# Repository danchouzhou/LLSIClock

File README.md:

# Nuvoton Visual Studio Code Template
## Usage
### To clone this project
This project work with submodule from Nuvoton corporation. You need to initialize submodules by passing ``--recurse-submodules`` to the ``git clone`` command.
```
git clone https://github.com/danchouzhou/Nuvoton-VScode-template.git --recurse-submodules
```

### Build tools
#### Windows users
Since we use VScode ``setting.json`` provide the build environment, only the execution binary need to be download (without installing). Download the following files, extract to the path ``C:\Users\"Your user name"\BuildTools\Windows`` which specific in ``.vscode/setting.json``.
- [gcc-arm-none-eabi-10.3-2021.07-win32.zip](https://developer.arm.com/downloads/-/gnu-rm)
- [xpack-windows-build-tools-4.3.0-1-win32-x64.zip
](https://github.com/xpack-dev-tools/windows-build-tools-xpack/releases/tag/v4.3.0-1)
- [OpenOCD-Nuvoton](https://github.com/OpenNuvoton/OpenOCD-Nuvoton/releases)
#### Linux users
- [gcc-arm-none-eabi-10.3-2021.07-x86_64-linux.tar.bz2](https://developer.arm.com/downloads/-/gnu-rm)
- [OpenOCD-Nuvoton](https://github.com/OpenNuvoton/OpenOCD-Nuvoton/releases)
```
mkdir -p ~/BuildTools/Linux/
tar jxvf gcc-arm-none-eabi-10.3-2021.07-x86_64-linux.tar.bz2 -C ~/BuildTools/Linux/
unzip OpenOCD_Linux.zip -d ~/BuildTools/Linux/
chmod +x ~/BuildTools/Linux/OpenOCD/bin/openocd
```
- GNU Make should be installed.
```
sudo apt install make
```
### Build the template
If you want to build the target for Nuvoton M480 series for example. Open a terminal inside the VScode.
```
cd firmware/LLSI_RGBW
```
Simply ``make``. ``LLSI_RGBW.bin`` should be inside the ``Objects`` folder.
```
make
```
### Flash the firmware
```
make flash
```
For Linux users, probably need to add the access permission for usb device.
```
sudo chmod -R 777 /dev/bus/usb/
```
### Rebuild
```
make clean
make
```

### Create your own project from this template
1. Add BSP submodule from [OpenNuvoton](https://github.com/OpenNuvoton). For example:
```
git submodule add https://github.com/OpenNuvoton/M480BSP.git NuMicro-M4/M480BSP
```
2. Edit ``CORTEX_M``, ``BASE``, ``DEVICE`` in the ``makefile.conf``.

## Reference
- [A Simple Makefile Tutorial](https://www.cs.colby.edu/maxwell/courses/tutorials/maketutor/)
- [Makefile Tutorial By Example](https://makefiletutorial.com/)
- [Git - Submodules](https://git-scm.com/book/en/v2/Git-Tools-Submodules)
- [Set global $PATH environment variable in VS Code - Stack Overflow](https://stackoverflow.com/questions/43983718/set-global-path-environment-variable-in-vs-code)
- [Flashing firmware with OpenOCD without using telnet](https://acassis.wordpress.com/2016/08/22/flashing-firmware-with-openocd-without-using-telnet/)

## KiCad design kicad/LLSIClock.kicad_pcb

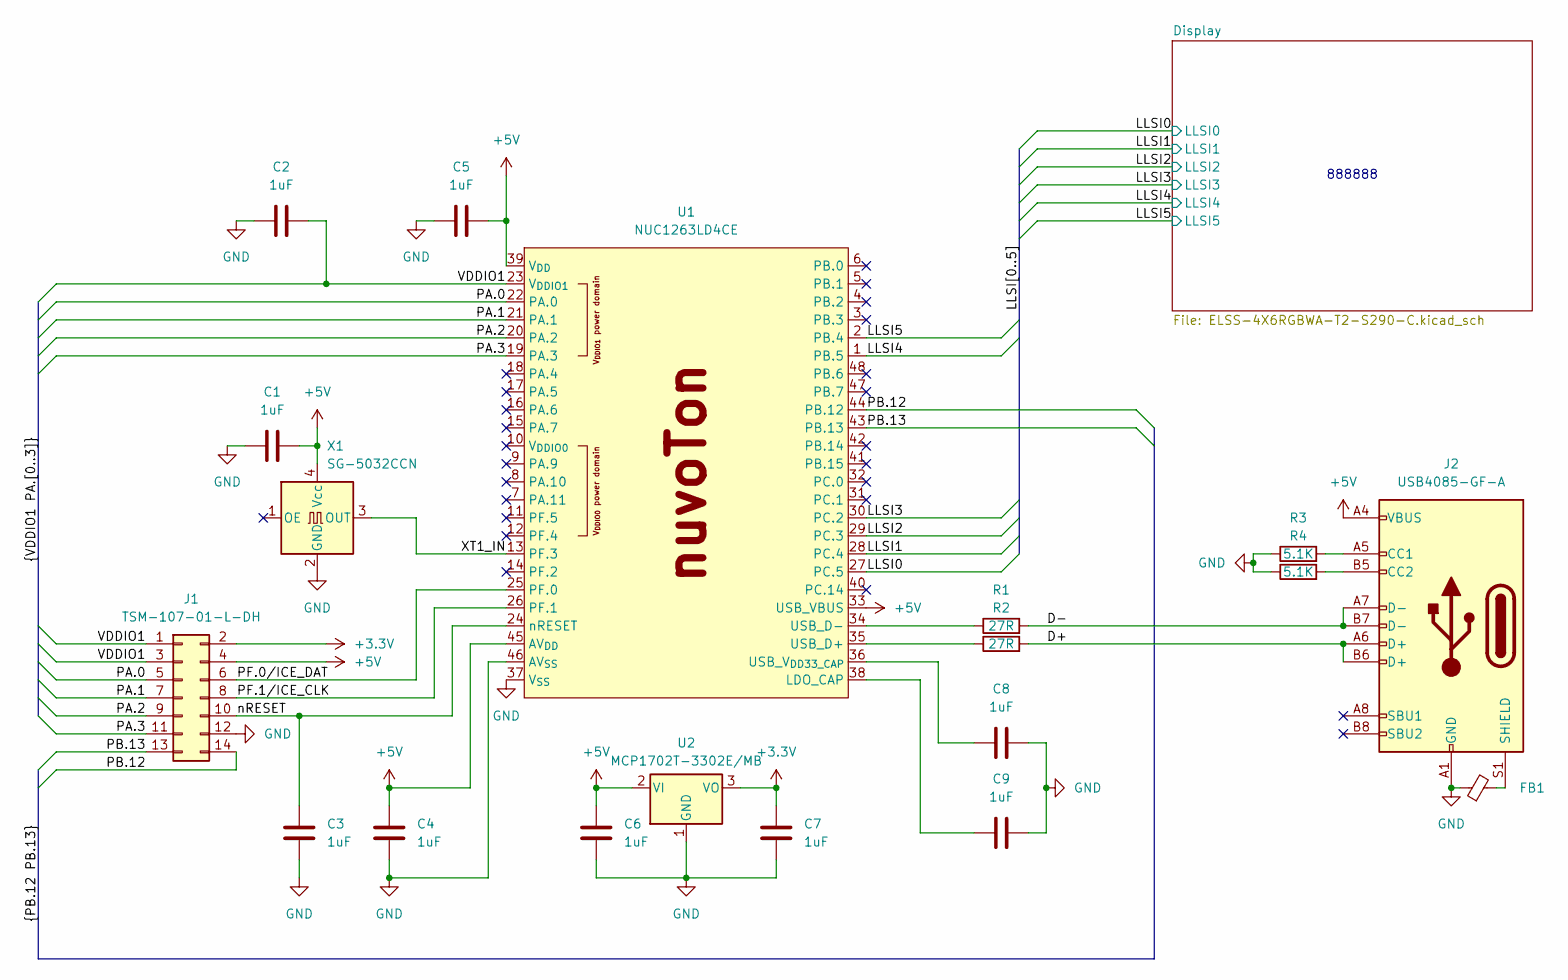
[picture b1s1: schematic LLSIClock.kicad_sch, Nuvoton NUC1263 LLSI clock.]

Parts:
C1, C2, C3, C4, C5, C6, C7, C8, C9: 1uF; C_0805_2012Metric
FB1: FerriteBead_Small; L_0805_2012Metric
J1: TSM-107-01-L-DH
J2: USB4085-GF-A; 2137160001_USB4085
R1, R2: 27R; R_0805_2012Metric
R3, R4: 5.1K; R_0805_2012Metric
U1: NUC1263LD4CE; LQFP-48_7x7mm_P0.5mm
U2: MCP1702T-3302E/MB; SOT-89-3
X1: SG-5032CCN; Oscillator_SMD_SeikoEpson_SG8002LB-4Pin_5.0x3.2mm

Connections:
+3.3V: C7.1, J1.2, U2.3 (VO)
+5V: C1.2, C4.1, C5.2, C6.1, J1.4, J2.A4 (VBUS), J2.A9 (VBUS), J2.B4 (VBUS), J2.B9 (VBUS), U1.33 (USB_VBUS), U1.39 (V_{DD}), U1.45 (AV_{DD}), U2.2 (VI), X1.4 (Vcc); also elsewhere on the board
/D+: J2.A6 (D+), J2.B6 (D+), R2.2
/D-: J2.A7 (D-), J2.B7 (D-), R1.2
/LLSI0: U1.27 (PC.5); also elsewhere on the board
/LLSI1: U1.28 (PC.4); also elsewhere on the board
/LLSI2: U1.29 (PC.3); also elsewhere on the board
/LLSI3: U1.30 (PC.2); also elsewhere on the board
/LLSI4: U1.1 (PB.5); also elsewhere on the board
/LLSI5: U1.2 (PB.4); also elsewhere on the board
/PA.0: J1.5, U1.22 (PA.0)
/PA.1: J1.7, U1.21 (PA.1)
/PA.2: J1.9, U1.20 (PA.2)
/PA.3: J1.11, U1.19 (PA.3)
/PB.12: J1.14, U1.44 (PB.12)
/PB.13: J1.13, U1.43 (PB.13)
/PF.0/ICE_DAT: J1.6, U1.25 (PF.0)
/PF.1/ICE_CLK: J1.8, U1.26 (PF.1)
/VDDIO1: C2.2, J1.1, J1.3, U1.23 (V_{DDIO1})
/XT1_IN: U1.13 (PF.3), X1.3 (OUT)
/nRESET: C3.1, J1.10, U1.24 (nRESET)
GND: C1.1, C2.1, C3.2, C4.2, C5.1, C6.2, C7.2, C8.2, C9.2, FB1.1, J1.12, J2.A1 (GND), J2.A12 (GND), J2.B1 (GND), J2.B12 (GND), R3.1, R4.1, U1.37 (V_{SS}), U1.46 (AV_{SS}), U2.1 (GND), X1.2 (GND); also elsewhere on the board
unnamed: J2.A5 (CC1), R3.2
unnamed: J2.B5 (CC2), R4.2
unnamed: FB1.2, J2.S1 (SHIELD)
unnamed: C9.1, U1.38 (LDO_CAP)
unnamed: R2.1, U1.35 (USB_D+)
unnamed: R1.1, U1.34 (USB_D-)
unnamed: C8.1, U1.36 (USB_V_{DD33_CAP})

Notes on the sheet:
888888

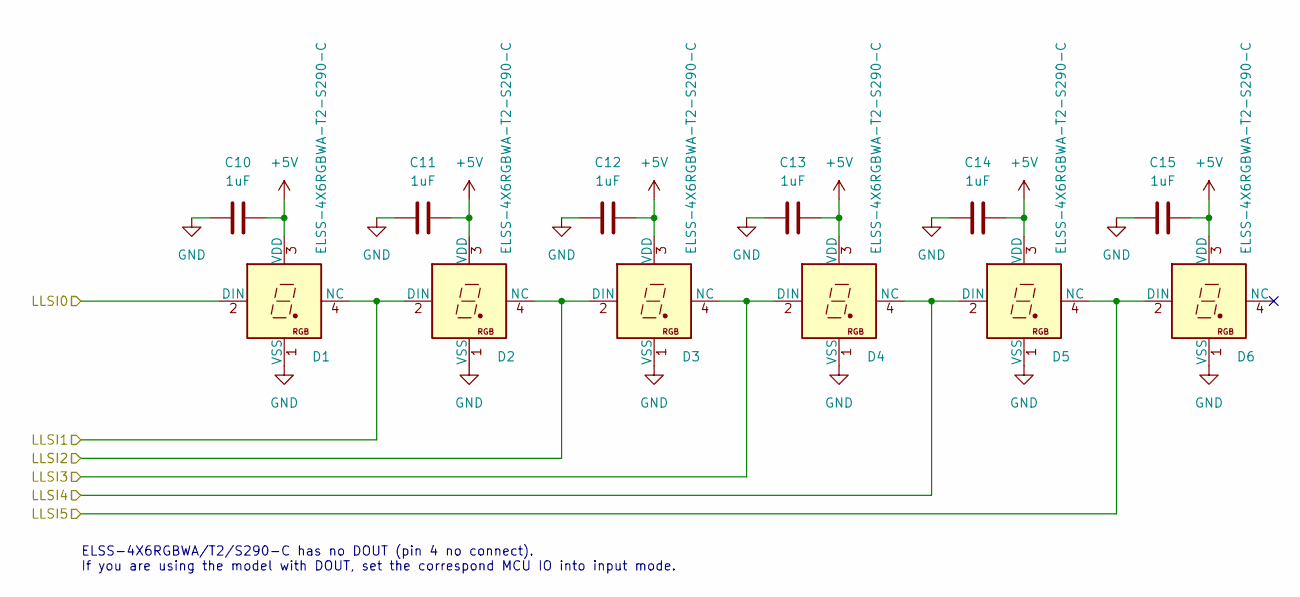
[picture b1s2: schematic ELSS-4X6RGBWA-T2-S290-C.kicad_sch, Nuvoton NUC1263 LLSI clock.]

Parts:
C10, C11, C12, C13, C14, C15: 1uF; C_0805_2012Metric
D1, D2, D3, D4, D5, D6: ELSS-4X6RGBWA-T2-S290-C

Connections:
+5V: C10.2, C11.2, C12.2, C13.2, C14.2, C15.2, D1.3 (VDD), D2.3 (VDD), D3.3 (VDD), D4.3 (VDD), D5.3 (VDD), D6.3 (VDD); also elsewhere on the board
/LLSI0: D1.2 (DIN); also elsewhere on the board
/LLSI1: D1.4 (NC), D2.2 (DIN); also elsewhere on the board
/LLSI2: D2.4 (NC), D3.2 (DIN); also elsewhere on the board
/LLSI3: D3.4 (NC), D4.2 (DIN); also elsewhere on the board
/LLSI4: D4.4 (NC), D5.2 (DIN); also elsewhere on the board
/LLSI5: D5.4 (NC), D6.2 (DIN); also elsewhere on the board
GND: C10.1, C11.1, C12.1, C13.1, C14.1, C15.1, D1.1 (VSS), D2.1 (VSS), D3.1 (VSS), D4.1 (VSS), D5.1 (VSS), D6.1 (VSS); also elsewhere on the board

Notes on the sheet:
ELSS-4X6RGBWA/T2/S290-C has no DOUT (pin 4 no connect). If you are using the model with DOUT, set the correspond MCU IO into input mode.

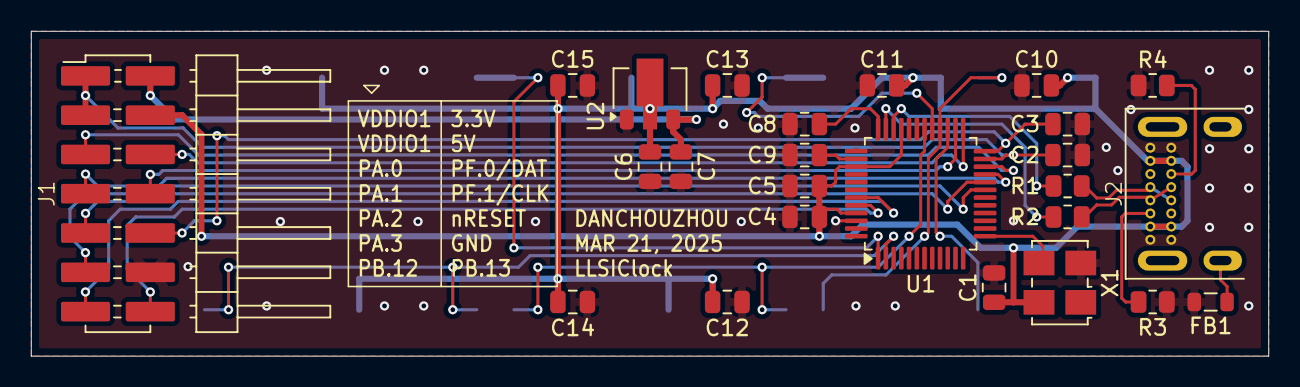
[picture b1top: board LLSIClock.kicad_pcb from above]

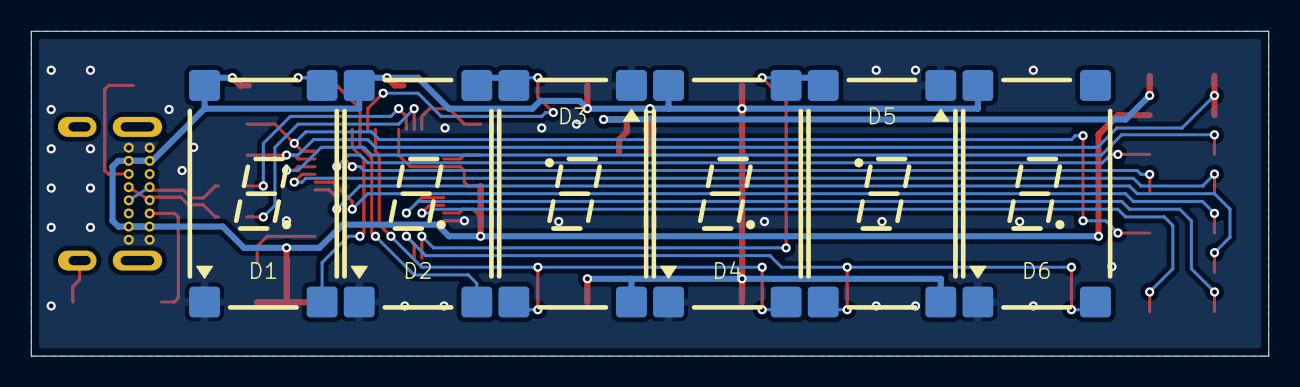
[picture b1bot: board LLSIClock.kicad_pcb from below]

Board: 2 copper layers, 80.0 x 21.0 mm, 31 parts (6 on the bottom side), 29 nets.

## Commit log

2025-03-28 1. Add LLSI_RGBW_PDMA
    2. Correct pixel count comment
    3. Update c_cpp_properties.json
2025-03-29 Add LLSI_RGB SampleCode
2025-03-31 Add KiCad files
2025-04-13 1. Update comment
    2. Remove file association from setting.json
2025-04-16 Remove unused string.h

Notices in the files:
kicad/ELSS-4X6RGBWA-T2-S290-C.kicad_sch:
Copyright © Danny Chou, all rights reserved.
